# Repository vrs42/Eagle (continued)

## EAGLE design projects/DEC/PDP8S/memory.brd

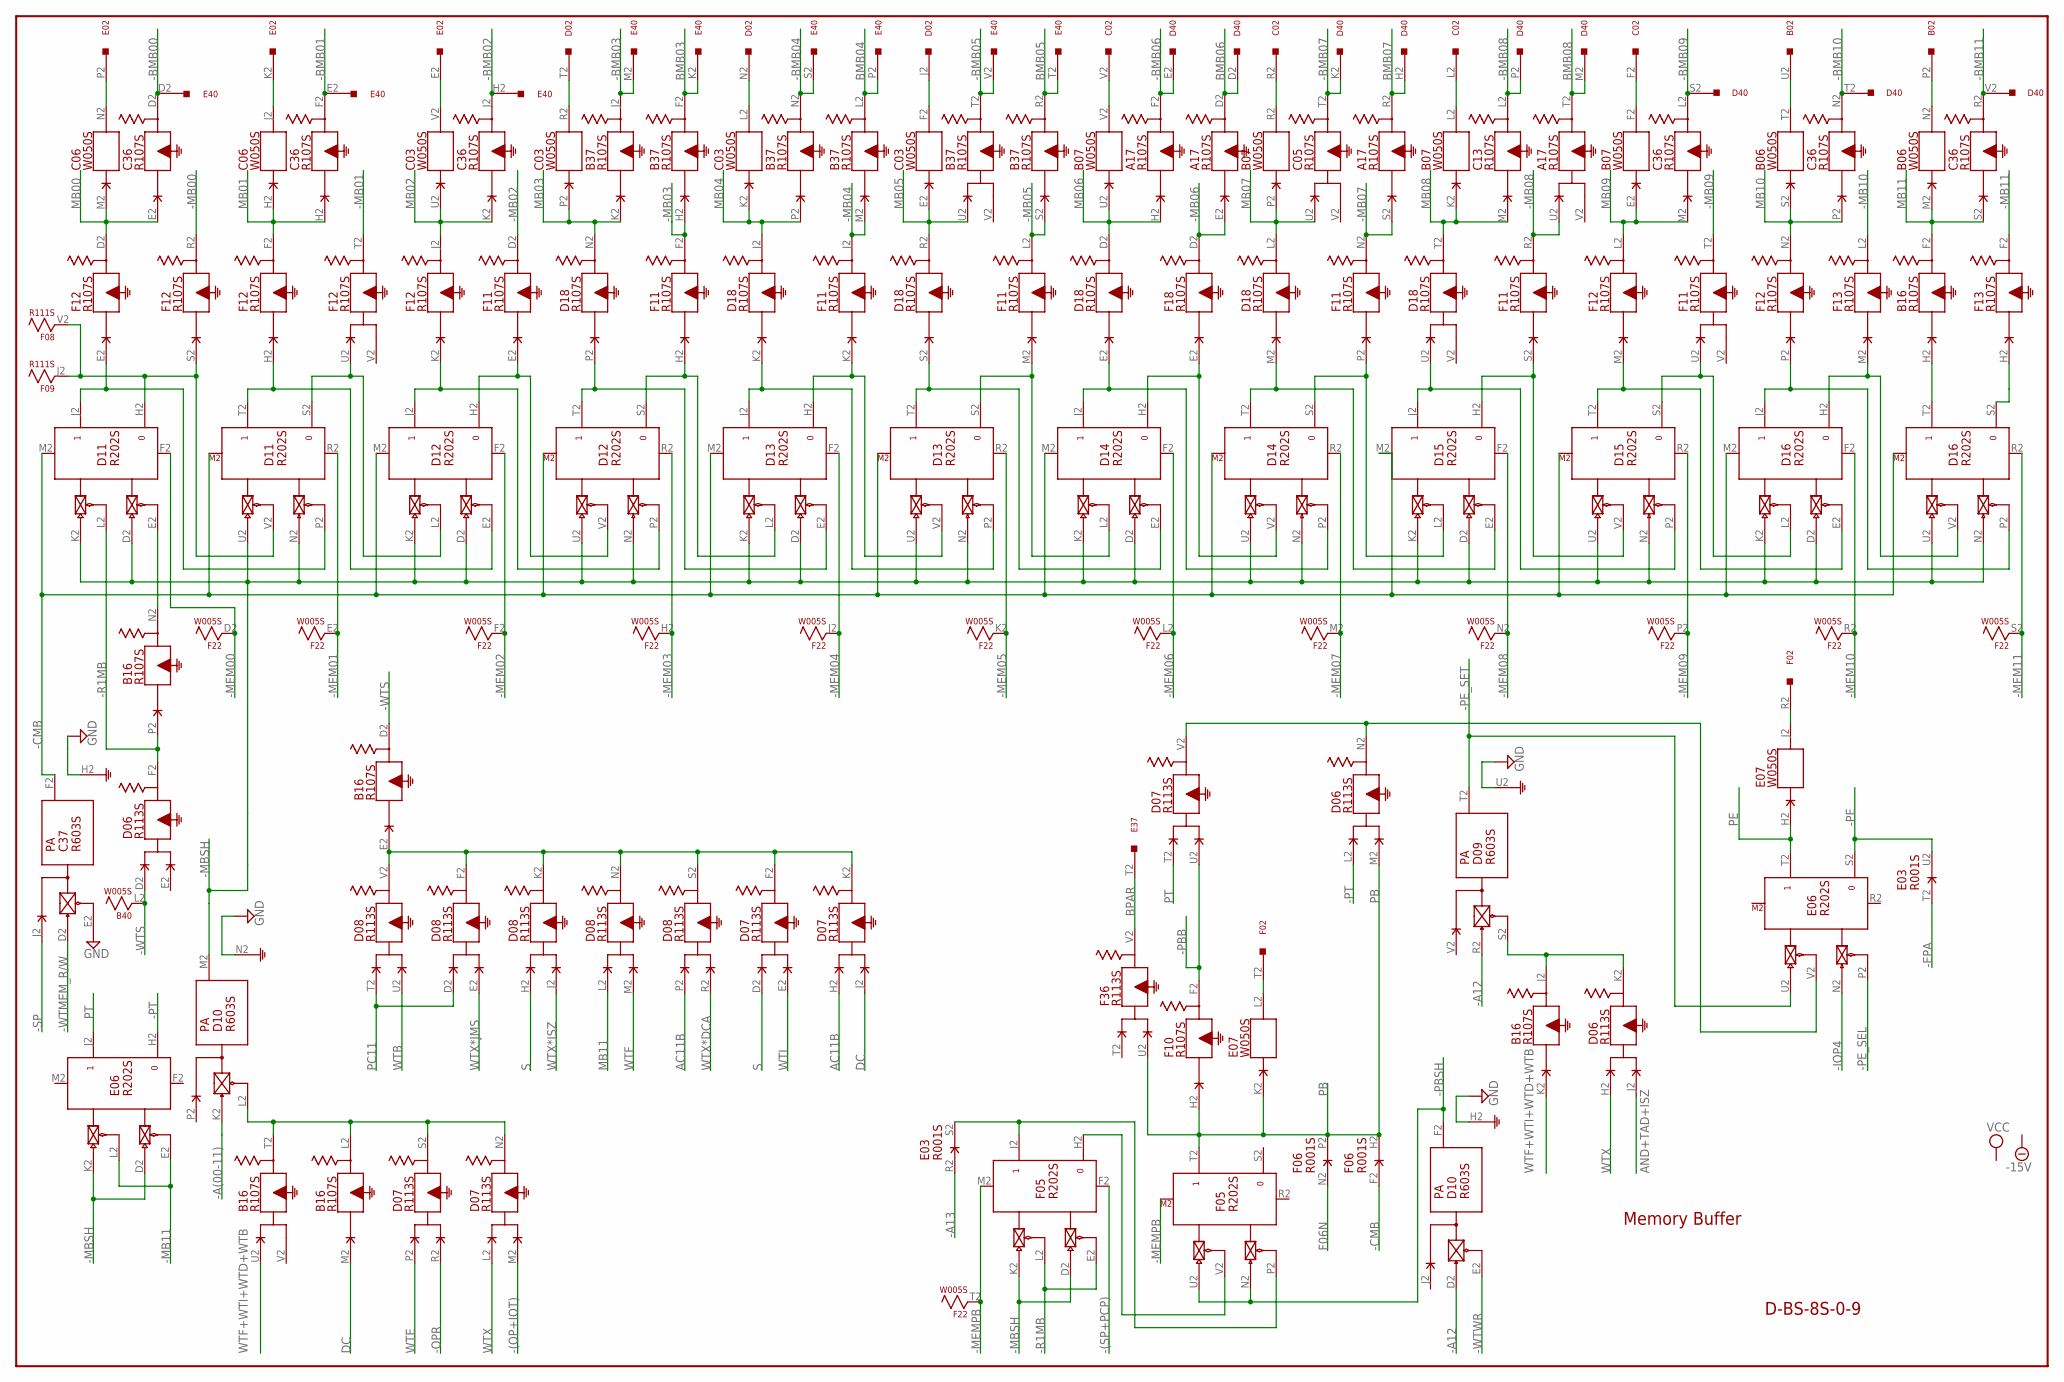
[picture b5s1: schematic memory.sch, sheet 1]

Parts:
A17: R107S; H807S
B02: W023S; H807S
B06, B07: W050S; H807S
B16, B37: R107S; H807S
B40: W005S; H807S
C02: W023S; H807S
C03, C06: W050S; H807S
C05, C13, C36: R107S; H807S
C37: R603S; H807S
D02: W023S; H807S
D06, D07, D08: R113S; H807S
D09, D10: R603S; H807S
D11, D12, D13, D14, D15, D16: R202S; H807S
D18: R107S; H807S
D40: W028S; H807S
E02: W023S; H807S
E03: R001S; H807S
E06: R202S; H807S
E07: W050S; H807S
E37, E40: W028S; H807S
F02: W023S; H807S
F05: R202S; H807S
F06: R001S; H807S
F08, F09: R111S; H807S
F10, F11, F12, F13, F18: R107S; H807S
F22: W005S; H807S
F36: R113S; H807S

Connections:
-15V: A17.B2 (-15V), B06.B2 (-15V), B07.B2 (-15V), B16.B2 (-15V), B37.B2 (-15V), B40.B2 (-15V), C03.B2 (-15V), C05.B2 (-15V), C06.B2 (-15V), C13.B2 (-15V), C36.B2 (-15V), C37.B2 (-15V), D06.B2 (-15V), D07.B2 (-15V), D08.B2 (-15V), D09.B2 (-15V), D10.B2 (-15V), D11.B2 (-15V), D12.B2 (-15V), D13.B2 (-15V), D14.B2 (-15V), D15.B2 (-15V), D16.B2 (-15V), D18.B2 (-15V), E03.B2 (-15V), E06.B2 (-15V), E07.B2 (-15V), F05.B2 (-15V), F06.B2 (-15V), F08.B2 (-15V), F09.B2 (-15V), F10.B2 (-15V), F11.B2 (-15V), F12.B2 (-15V), F13.B2 (-15V), F18.B2 (-15V), F22.B2 (-15V), F36.B2 (-15V); also elsewhere on the board
-(OP+IOT): D07.M2; also elsewhere on the board
-(SP+PCP): F05.F2 (RESET); also elsewhere on the board
-A12: D09.R2 (PU0), D10.D2 (PU0); also elsewhere on the board
-A13: E03.R2 (D); also elsewhere on the board
-A(00-11): D10.K2 (PU0); also elsewhere on the board
-BMB00: C36.D2, E40.D2
-BMB01: C36.F2, E40.E2
-BMB02: C36.J2, E40.H2
-BMB03: B37.J2, E40.M2
-BMB04: B37.N2, E40.S2
-BMB05: B37.T2, E40.V2
-BMB06: A17.F2, D40.E2
-BMB07: C05.T2, D40.K2
-BMB08: C13.L2, D40.P2
-BMB09: C36.L2, D40.S2
-BMB10: C36.N2, D40.T2
-BMB11: C36.R2, D40.V2
-CMB: C37.F2 (O), D11.M2 (SET), D12.M2 (SET), D13.M2 (SET), D14.M2 (SET), D15.M2 (SET), D16.M2 (SET), F06.F2 (D)
-EPA: E03.T2 (D); also elsewhere on the board
-IOP4: E06.N2 (PU0); also elsewhere on the board
-MB00: F12.R2; also elsewhere on the board
-MB01: F12.T2; also elsewhere on the board
-MB02: F11.D2; also elsewhere on the board
-MB03: B37.H2, F11.F2; also elsewhere on the board
-MB04: B37.M2, F11.J2; also elsewhere on the board
-MB05: B37.S2, F11.L2; also elsewhere on the board
-MB06: A17.E2, F18.D2; also elsewhere on the board
-MB07: A17.S2, F11.N2; also elsewhere on the board
-MB08: A17.U2, F11.R2; also elsewhere on the board
-MB09: F11.T2; also elsewhere on the board
-MB10: F13.L2; also elsewhere on the board
-MB11: E06.E2 (EN0), E06.L2 (EN1), F13.F2; also elsewhere on the board
-MBSH: D10.M2 (O), D11.D2 (PU0), D11.K2 (PU1), D11.N2 (PU0), D11.U2 (PU1), D12.D2 (PU0), D12.K2 (PU1), D12.N2 (PU0), D12.U2 (PU1), D13.D2 (PU0), D13.K2 (PU1), D13.N2 (PU0), D13.U2 (PU1), D14.D2 (PU0), D14.K2 (PU1), D14.N2 (PU0), D14.U2 (PU1), D15.D2 (PU0), D15.K2 (PU1), D15.N2 (PU0), D15.U2 (PU1), D16.D2 (PU0), D16.K2 (PU1), D16.N2 (PU0), D16.U2 (PU1), E06.D2 (PU0), E06.K2 (PU1), F05.D2 (PU0), F05.K2 (PU1)
-MEM00: D11.F2 (RESET), F22.D2; also elsewhere on the board
-MEM01: D11.R2 (RESET), F22.E2; also elsewhere on the board
-MEM02: D12.F2 (RESET), F22.F2; also elsewhere on the board
-MEM03: D12.R2 (RESET), F22.H2; also elsewhere on the board
-MEM04: D13.F2 (RESET), F22.J2; also elsewhere on the board
-MEM05: D13.R2 (RESET), F22.K2; also elsewhere on the board
-MEM06: D14.F2 (RESET), F22.L2; also elsewhere on the board
-MEM07: D14.R2 (RESET), F22.M2; also elsewhere on the board
-MEM08: D15.F2 (RESET), F22.N2; also elsewhere on the board
-MEM09: D15.R2 (RESET), F22.P2; also elsewhere on the board
-MEM10: D16.F2 (RESET), F22.R2; also elsewhere on the board
-MEM11: D16.R2 (RESET), F22.S2; also elsewhere on the board
-MEMPB: F05.M2 (SET), F22.T2; also elsewhere on the board
-OPR: D07.R2; also elsewhere on the board
-PBB: D07.U2, F10.F2; also elsewhere on the board
-PBSH: D10.F2 (O), F05.N2 (PU0), F05.U2 (PU1)
-PE: E03.U2 (E), E06.S2 (0); also elsewhere on the board
-PE_SEL: E06.P2 (EN0); also elsewhere on the board
-PE_SET: D09.T2 (O), E06.U2 (PU1)
-PT: D06.L2, E06.H2 (0)
-R1MB: B16.P2, D06.F2, D11.L2 (EN1), F05.E2 (EN0), F05.L2 (EN1)
-SP: C37.J2; also elsewhere on the board
-WTMEM_R/W: C37.D2 (PU0); also elsewhere on the board
-WTS: B16.D2, B40.L2, D06.D2; also elsewhere on the board
-WTWR: D10.E2 (EN0); also elsewhere on the board
AC11B: D07.H2, D08.P2; also elsewhere on the board
AND+TAD+ISZ: D06.J2; also elsewhere on the board
BMB03: B37.F2, E40.K2
BMB04: B37.L2, E40.P2
BMB05: B37.R2, E40.T2
BMB06: A17.D2, D40.D2
BMB07: A17.R2, D40.H2
BMB08: A17.T2, D40.M2
BPAR: E37.T2, F36.V2
DC: B16.M2, D07.J2; also elsewhere on the board
F06N: F06.N2 (D)
GND: A17.C2 (GND), B06.C2 (GND), B07.C2 (GND), B16.C2 (GND), B37.C2 (GND), B40.C2 (GND), C03.C2 (GND), C05.C2 (GND), C06.C2 (GND), C13.C2 (GND), C36.C2 (GND), C37.C2 (GND), C37.E2 (EN0), C37.H2 (G), D06.C2 (GND), D07.C2 (GND), D08.C2 (GND), D09.C2 (GND), D09.U2 (G), D10.C2 (GND), D10.H2 (G), D10.N2 (G), D11.C2 (GND), D12.C2 (GND), D13.C2 (GND), D14.C2 (GND), D15.C2 (GND), D16.C2 (GND), D18.C2 (GND), D40.C2 (GND), D40.F2 (GND), D40.J2 (GND), D40.L2 (GND), D40.N2 (GND), D40.R2 (GND), D40.U2 (GND), E03.C2 (GND), E06.C2 (GND), E07.C2 (GND), E37.C2 (GND), E37.F2 (GND), E37.J2 (GND), E37.L2 (GND), E37.N2 (GND), E37.R2 (GND), E37.U2 (GND), E40.C2 (GND), E40.F2 (GND), E40.J2 (GND), E40.L2 (GND), E40.N2 (GND), E40.R2 (GND), E40.U2 (GND), F05.C2 (GND), F06.C2 (GND), F08.C2 (GND), F09.C2 (GND), F10.C2 (GND), F11.C2 (GND), F12.C2 (GND), F13.C2 (GND), F18.C2 (GND), F22.C2 (GND), F36.C2 (GND); also elsewhere on the board
MB00: C06.M2, C36.E2, F12.D2
MB01: C06.H2, C36.H2, F12.F2
MB02: C03.U2, C36.K2, F12.J2
MB03: B37.K2, C03.P2, D18.N2
MB04: B37.P2, C03.K2, D18.J2; also elsewhere on the board
MB05: B37.U2, C03.E2, D18.R2; also elsewhere on the board
MB06: A17.H2, B07.U2, D18.D2; also elsewhere on the board
MB07: B07.P2, C05.U2, D18.L2; also elsewhere on the board
MB08: B07.K2, C13.M2, D18.T2; also elsewhere on the board
MB09: B07.E2, C36.M2, F12.L2; also elsewhere on the board
MB10: B06.S2, C36.P2, F12.N2; also elsewhere on the board
MB11: B06.M2, B16.F2, C36.S2, D08.L2; also elsewhere on the board
unnamed: D11.J2 (1), D11.P2 (EN0), F12.E2
unnamed: C06.N2, E02.P2
unnamed: D11.H2 (0), D11.V2 (EN1), F08.V2, F09.J2, F12.S2
unnamed: D11.T2 (1), D12.E2 (EN0), F12.H2
unnamed: B16.E2, D07.F2, D07.K2, D08.F2, D08.K2, D08.N2, D08.S2, D08.V2
unnamed: D12.J2 (1), D12.P2 (EN0), F12.K2
unnamed: D12.T2 (1), D13.E2 (EN0), D18.P2
unnamed: D13.J2 (1), D13.P2 (EN0), D18.K2
unnamed: D13.T2 (1), D14.E2 (EN0), D18.S2
unnamed: D14.J2 (1), D14.P2 (EN0), D18.E2
unnamed: D14.T2 (1), D15.E2 (EN0), D18.M2
unnamed: D15.J2 (1), D15.P2 (EN0), D18.U2
unnamed: D15.H2 (0), D15.V2 (EN1), F11.S2
unnamed: D14.S2 (0), D15.L2 (EN1), F11.P2
unnamed: D14.H2 (0), D14.V2 (EN1), F18.E2
unnamed: D13.S2 (0), D14.L2 (EN1), F11.M2
unnamed: D15.T2 (1), D16.E2 (EN0), F12.M2
unnamed: D15.S2 (0), D16.L2 (EN1), F11.U2
unnamed: D16.J2 (1), D16.P2 (EN0), F12.P2
unnamed: D13.H2 (0), D13.V2 (EN1), F11.K2
unnamed: D12.S2 (0), D13.L2 (EN1), F11.H2
unnamed: D12.H2 (0), D12.V2 (EN1), F11.E2
unnamed: D11.S2 (0), D12.L2 (EN1), F12.U2
unnamed: D16.H2 (0), D16.V2 (EN1), F13.M2
unnamed: B16.H2, D16.T2 (1)
unnamed: D16.S2 (0), F13.H2
unnamed: C06.J2, E02.K2
unnamed: C03.V2, E02.E2
unnamed: C03.R2, D02.T2
unnamed: C03.L2, D02.N2
unnamed: C03.F2, D02.J2
unnamed: B07.V2, C02.V2
unnamed: B07.R2, C02.R2
unnamed: B07.L2, C02.L2
unnamed: B07.F2, C02.F2
unnamed: B02.U2, B06.T2
unnamed: B02.P2, B06.N2
unnamed: B16.L2, B16.T2, D07.N2, D07.S2, D10.L2 (EN0)
unnamed: B16.N2, D11.E2 (EN0)
unnamed: B16.J2, D06.K2, D09.S2 (EN0)
unnamed: E07.J2, F02.R2
unnamed: D06.N2, D07.V2, E06.V2 (EN1)
unnamed: E07.L2, F02.T2
unnamed: F05.H2 (0), F05.V2 (EN1)
unnamed: E03.S2 (E), F05.J2 (1), F05.P2 (EN0)
PB: D06.M2, E07.K2, F05.T2 (1), F06.H2 (E), F06.P2 (E), F10.H2, F36.U2
PC11: D08.D2, D08.T2; also elsewhere on the board
PE: E06.T2 (1), E07.H2; also elsewhere on the board
PT: D07.T2, E06.J2 (1)
S: D07.D2, D08.H2; also elsewhere on the board
VCC: A17.A2 (VCC), B06.A2 (VCC), B07.A2 (VCC), B16.A2 (VCC), B37.A2 (VCC), B40.A2 (VCC), C03.A2 (VCC), C05.A2 (VCC), C06.A2 (VCC), C13.A2 (VCC), C36.A2 (VCC), C37.A2 (VCC), D06.A2 (VCC), D07.A2 (VCC), D08.A2 (VCC), D09.A2 (VCC), D10.A2 (VCC), D11.A2 (VCC), D12.A2 (VCC), D13.A2 (VCC), D14.A2 (VCC), D15.A2 (VCC), D16.A2 (VCC), D18.A2 (VCC), E03.A2 (VCC), E06.A2 (VCC), E07.A2 (VCC), F05.A2 (VCC), F06.A2 (VCC), F08.A2 (VCC), F09.A2 (VCC), F10.A2 (VCC), F11.A2 (VCC), F12.A2 (VCC), F13.A2 (VCC), F18.A2 (VCC), F22.A2 (VCC), F36.A2 (VCC); also elsewhere on the board
WTB: D08.U2; also elsewhere on the board
WTE: D07.P2; also elsewhere on the board
WTF: D08.M2; also elsewhere on the board
WTF+WTI+WTD+WTB: B16.K2, B16.U2; also elsewhere on the board
WTI: D07.E2; also elsewhere on the board
WTX: D06.H2, D07.L2; also elsewhere on the board
WTX*DCA: D08.R2; also elsewhere on the board
WTX*ISZ: D08.J2; also elsewhere on the board
WTX*JMS: D08.E2; also elsewhere on the board

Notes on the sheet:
D-BS-8S-0-9
Memory Buffer

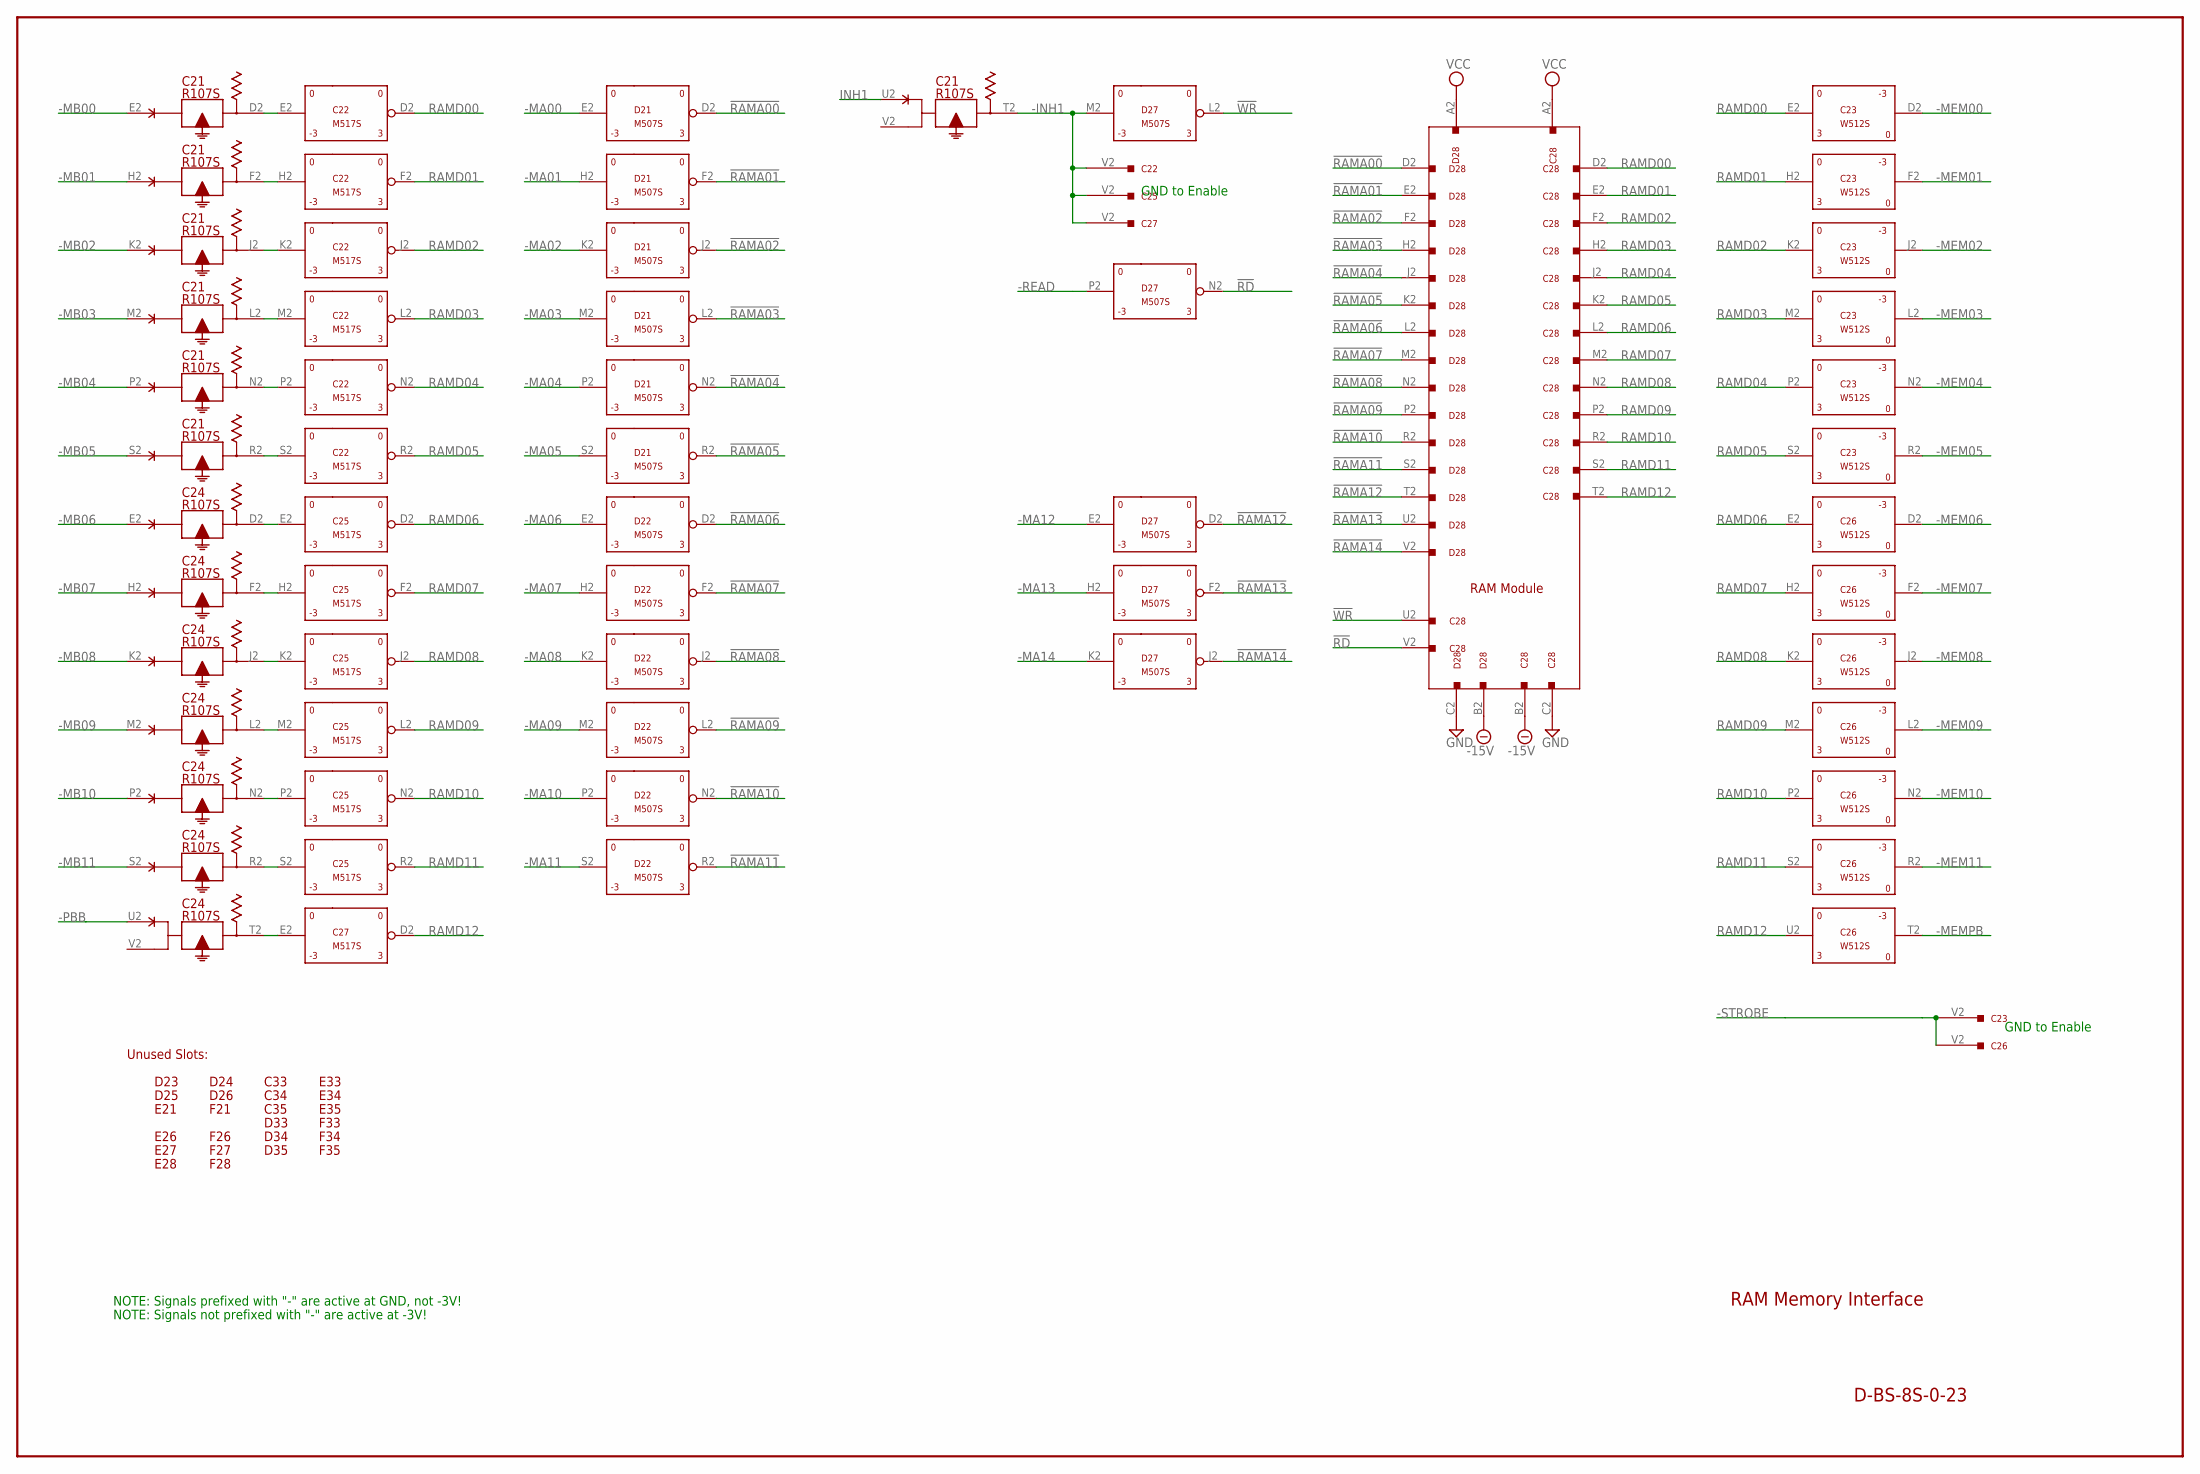
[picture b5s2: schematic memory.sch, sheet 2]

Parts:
C21, C24: R107S; H807S
C22, C25, C27: M517S; H807S
C23, C26: W512S; H807S
C28: W023S; H807S
C33, C34, C35: EMPTYS; H807S
D21, D22, D27: M507S; H807S
D23, D24, D25, D26, D33, D34, D35: EMPTYS; H807S
D28: W023S; H807S
E21, E26, E27, E28, E33, E34, E35: EMPTYS; H807S
F21, F26, F27, F28, F33, F34, F35: EMPTYS; H807S

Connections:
!RAMA00: D21.D2 (OUT), D28.D2
!RAMA01: D21.F2 (OUT), D28.E2
!RAMA02: D21.J2 (OUT), D28.F2
!RAMA03: D21.L2 (OUT), D28.H2
!RAMA04: D21.N2 (OUT), D28.J2
!RAMA05: D21.R2 (OUT), D28.K2
!RAMA06: D22.D2 (OUT), D28.L2
!RAMA07: D22.F2 (OUT), D28.M2
!RAMA08: D22.J2 (OUT), D28.N2
!RAMA09: D22.L2 (OUT), D28.P2
!RAMA10: D22.N2 (OUT), D28.R2
!RAMA11: D22.R2 (OUT), D28.S2
!RAMA12: D27.D2 (OUT), D28.T2
!RAMA13: D27.F2 (OUT), D28.U2
!RAMA14: D27.J2 (OUT), D28.V2
!RD: C28.V2, D27.N2 (OUT)
!WR: C28.U2, D27.L2 (OUT)
-15V: C21.B2 (-15V), C22.B2 (-15V), C23.B2 (-15V), C24.B2 (-15V), C25.B2 (-15V), C26.B2 (-15V), C27.B2 (-15V), C28.B2, C33.B2 (-15V), C34.B2 (-15V), C35.B2 (-15V), D21.B2 (-15V), D22.B2 (-15V), D23.B2 (-15V), D24.B2 (-15V), D25.B2 (-15V), D26.B2 (-15V), D27.B2 (-15V), D28.B2, D33.B2 (-15V), D34.B2 (-15V), D35.B2 (-15V), E21.B2 (-15V), E26.B2 (-15V), E27.B2 (-15V), E28.B2 (-15V), E33.B2 (-15V), E34.B2 (-15V), E35.B2 (-15V), F21.B2 (-15V), F26.B2 (-15V), F27.B2 (-15V), F28.B2 (-15V), F33.B2 (-15V), F34.B2 (-15V), F35.B2 (-15V); also elsewhere on the board
-INH1: C21.T2, C22.V2, C25.V2, C27.V2, D27.M2 (IN)
-MA00: D21.E2 (IN); also elsewhere on the board
-MA01: D21.H2 (IN); also elsewhere on the board
-MA02: D21.K2 (IN); also elsewhere on the board
-MA03: D21.M2 (IN); also elsewhere on the board
-MA04: D21.P2 (IN); also elsewhere on the board
-MA05: D21.S2 (IN); also elsewhere on the board
-MA06: D22.E2 (IN); also elsewhere on the board
-MA07: D22.H2 (IN); also elsewhere on the board
-MA08: D22.K2 (IN); also elsewhere on the board
-MA09: D22.M2 (IN); also elsewhere on the board
-MA10: D22.P2 (IN); also elsewhere on the board
-MA11: D22.S2 (IN); also elsewhere on the board
-MA12: D27.E2 (IN)
-MA13: D27.H2 (IN)
-MA14: D27.K2 (IN)
-MB00: C21.E2; also elsewhere on the board
-MB01: C21.H2; also elsewhere on the board
-MB02: C21.K2; also elsewhere on the board
-MB03: C21.M2; also elsewhere on the board
-MB04: C21.P2; also elsewhere on the board
-MB05: C21.S2; also elsewhere on the board
-MB06: C24.E2; also elsewhere on the board
-MB07: C24.H2; also elsewhere on the board
-MB08: C24.K2; also elsewhere on the board
-MB09: C24.M2; also elsewhere on the board
-MB10: C24.P2; also elsewhere on the board
-MB11: C24.S2; also elsewhere on the board
-MEM00: C23.D2 (OUT); also elsewhere on the board
-MEM01: C23.F2 (OUT); also elsewhere on the board
-MEM02: C23.J2 (OUT); also elsewhere on the board
-MEM03: C23.L2 (OUT); also elsewhere on the board
-MEM04: C23.N2 (OUT); also elsewhere on the board
-MEM05: C23.R2 (OUT); also elsewhere on the board
-MEM06: C26.D2 (OUT); also elsewhere on the board
-MEM07: C26.F2 (OUT); also elsewhere on the board
-MEM08: C26.J2 (OUT); also elsewhere on the board
-MEM09: C26.L2 (OUT); also elsewhere on the board
-MEM10: C26.N2 (OUT); also elsewhere on the board
-MEM11: C26.R2 (OUT); also elsewhere on the board
-MEMPB: C26.T2 (OUT); also elsewhere on the board
-PBB: C24.U2; also elsewhere on the board
-READ: D27.P2 (IN); also elsewhere on the board
-STROBE: C23.V2, C26.V2; also elsewhere on the board
GND: C21.C2 (GND), C22.C2 (GND), C22.T2 (GND), C22.U2 (GND), C23.C2 (GND), C24.C2 (GND), C25.C2 (GND), C25.T2 (GND), C25.U2 (GND), C26.C2 (GND), C27.C2 (GND), C27.T2 (GND), C27.U2 (GND), C28.C2, C33.C2 (GND), C34.C2 (GND), C35.C2 (GND), D21.C2 (GND), D22.C2 (GND), D23.C2 (GND), D24.C2 (GND), D25.C2 (GND), D26.C2 (GND), D27.C2 (GND), D28.C2, D33.C2 (GND), D34.C2 (GND), D35.C2 (GND), E21.C2 (GND), E26.C2 (GND), E27.C2 (GND), E28.C2 (GND), E33.C2 (GND), E34.C2 (GND), E35.C2 (GND), F21.C2 (GND), F26.C2 (GND), F27.C2 (GND), F28.C2 (GND), F33.C2 (GND), F34.C2 (GND), F35.C2 (GND); also elsewhere on the board
INH1: C21.U2; also elsewhere on the board
unnamed: C24.D2, C25.E2 (IN)
unnamed: C21.R2, C22.S2 (IN)
unnamed: C21.N2, C22.P2 (IN)
unnamed: C21.L2, C22.M2 (IN)
unnamed: C21.J2, C22.K2 (IN)
unnamed: C21.F2, C22.H2 (IN)
unnamed: C21.D2, C22.E2 (IN)
unnamed: C24.F2, C25.H2 (IN)
unnamed: C24.J2, C25.K2 (IN)
unnamed: C24.L2, C25.M2 (IN)
unnamed: C24.N2, C25.P2 (IN)
unnamed: C24.R2, C25.S2 (IN)
unnamed: C24.T2, C27.E2 (IN)
RAMD00: C22.D2 (OUT), C23.E2 (IN), C28.D2
RAMD01: C22.F2 (OUT), C23.H2 (IN), C28.E2
RAMD02: C22.J2 (OUT), C23.K2 (IN), C28.F2
RAMD03: C22.L2 (OUT), C23.M2 (IN), C28.H2
RAMD04: C22.N2 (OUT), C23.P2 (IN), C28.J2
RAMD05: C22.R2 (OUT), C23.S2 (IN), C28.K2
RAMD06: C25.D2 (OUT), C26.E2 (IN), C28.L2
RAMD07: C25.F2 (OUT), C26.H2 (IN), C28.M2
RAMD08: C25.J2 (OUT), C26.K2 (IN), C28.N2
RAMD09: C25.L2 (OUT), C26.M2 (IN), C28.P2
RAMD10: C25.N2 (OUT), C26.P2 (IN), C28.R2
RAMD11: C25.R2 (OUT), C26.S2 (IN), C28.S2
RAMD12: C26.U2 (IN), C27.D2 (OUT), C28.T2
VCC: C21.A2 (VCC), C22.A2 (VCC), C23.A2 (VCC), C24.A2 (VCC), C25.A2 (VCC), C26.A2 (VCC), C27.A2 (VCC), C28.A2, C33.A2 (VCC), C34.A2 (VCC), C35.A2 (VCC), D21.A2 (VCC), D22.A2 (VCC), D23.A2 (VCC), D24.A2 (VCC), D25.A2 (VCC), D26.A2 (VCC), D27.A2 (VCC), D28.A2, D33.A2 (VCC), D34.A2 (VCC), D35.A2 (VCC), E21.A2 (VCC), E26.A2 (VCC), E27.A2 (VCC), E28.A2 (VCC), E33.A2 (VCC), E34.A2 (VCC), E35.A2 (VCC), F21.A2 (VCC), F26.A2 (VCC), F27.A2 (VCC), F28.A2 (VCC), F33.A2 (VCC), F34.A2 (VCC), F35.A2 (VCC); also elsewhere on the board

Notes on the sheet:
RAM Module
Unused Slots:
GND to Enable
NOTE: Signals prefixed with "-" are active at GND, not -3V!
NOTE: Signals not prefixed with "-" are active at -3V!
D-BS-8S-0-23
RAM Memory Interface

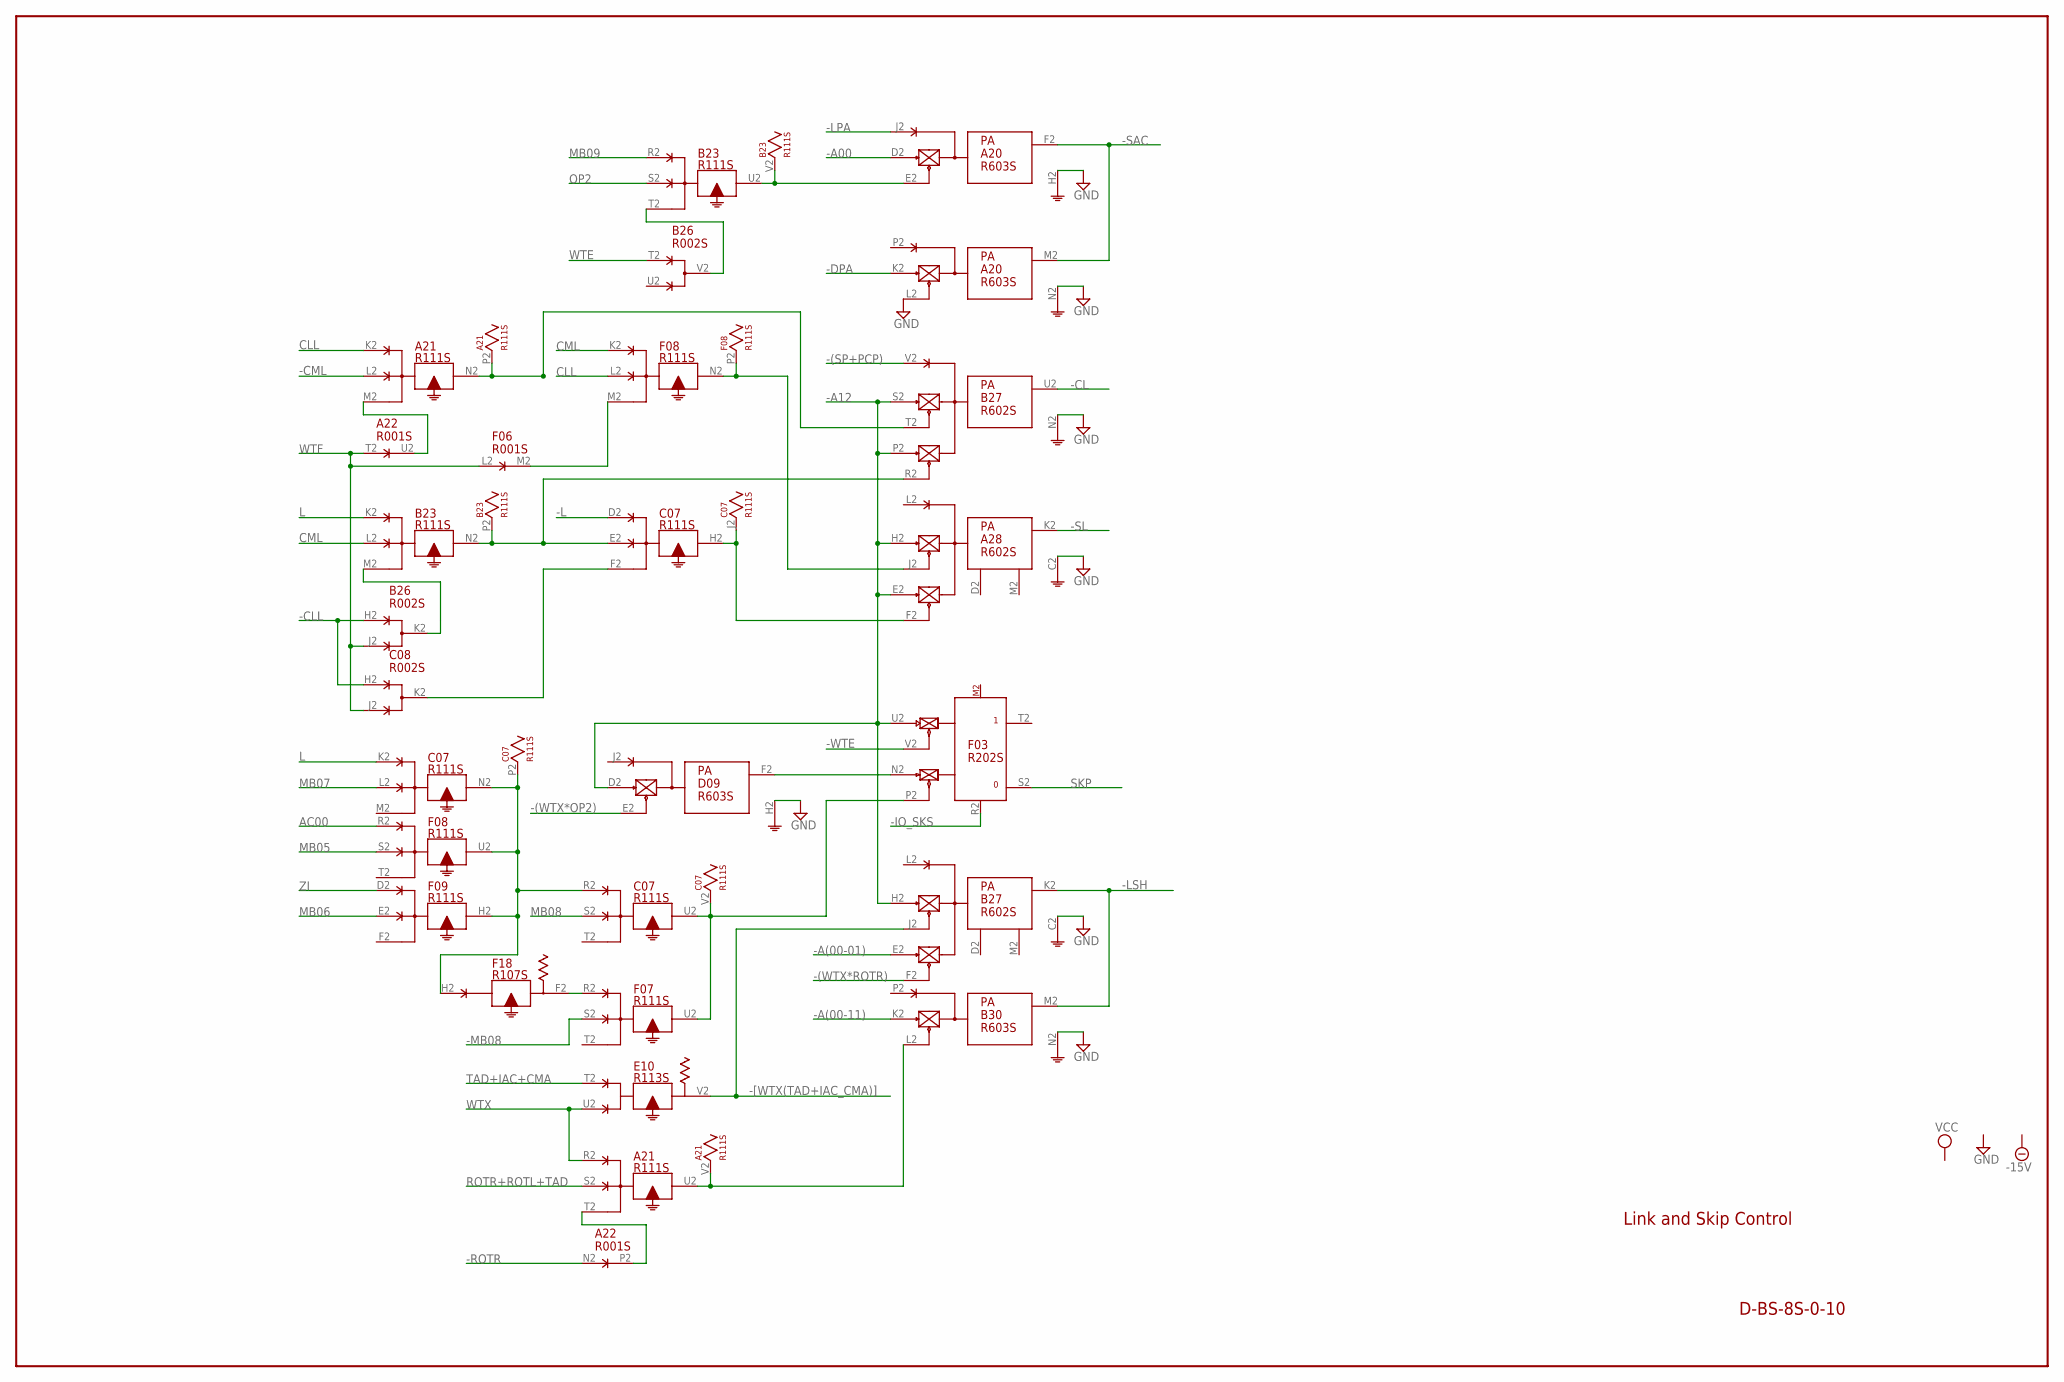
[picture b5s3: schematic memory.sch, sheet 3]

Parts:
A20: R603S; H807S
A21: R111S; H807S
A22: R001S; H807S
A28: R602S; H807S
B23: R111S; H807S
B26: R002S; H807S
B27: R602S; H807S
B30: R603S; H807S
C07: R111S; H807S
C08: R002S; H807S
D09: R603S; H807S
E10: R113S; H807S
F03: R202S; H807S
F06: R001S; H807S
F07, F08, F09: R111S; H807S
F18: R107S; H807S

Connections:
-15V: A20.B2 (-15V), A21.B2 (-15V), A22.B2 (-15V), A28.B2 (-15V), B23.B2 (-15V), B26.B2 (-15V), B27.B2 (-15V), B30.B2 (-15V), C07.B2 (-15V), C08.B2 (-15V), D09.B2 (-15V), E10.B2 (-15V), F03.B2 (-15V), F06.B2 (-15V), F07.B2 (-15V), F08.B2 (-15V), F09.B2 (-15V), F18.B2 (-15V); also elsewhere on the board
-(SP+PCP): B27.V2 (L); also elsewhere on the board
-(WTX*OP2): D09.E2 (EN0); also elsewhere on the board
-(WTX*ROTR): B27.F2 (F); also elsewhere on the board
-A00: A20.D2 (PU0); also elsewhere on the board
-A12: A28.E2 (E), A28.H2 (H), B27.H2 (H), B27.P2 (E), B27.S2 (H), D09.D2 (PU0), F03.U2 (PU1); also elsewhere on the board
-A(00-01): B27.E2 (E); also elsewhere on the board
-A(00-11): B30.K2 (PU0); also elsewhere on the board
-CL: B27.U2 (K); also elsewhere on the board
-CLL: B26.H2 (D), C08.H2 (D); also elsewhere on the board
-CML: A21.L2; also elsewhere on the board
-DPA: A20.K2 (PU0); also elsewhere on the board
-IO_SKS: F03.R2 (RESET); also elsewhere on the board
-L: C07.D2; also elsewhere on the board
-LPA: A20.J2; also elsewhere on the board
-LSH: B27.K2 (K), B30.M2 (O); also elsewhere on the board
-MB08: F07.S2; also elsewhere on the board
-ROTR: A22.N2 (D); also elsewhere on the board
-SAC: A20.F2 (O), A20.M2 (O); also elsewhere on the board
-SL: A28.K2 (K); also elsewhere on the board
-WTE: F03.V2 (EN1); also elsewhere on the board
-[WTX(TAD+IAC_CMA)]: B27.J2 (J), E10.V2
AC00: F08.R2; also elsewhere on the board
CLL: A21.K2, F08.L2; also elsewhere on the board
CML: B23.L2, F08.K2; also elsewhere on the board
GND: A20.C2 (GND), A20.H2 (G), A20.L2 (EN0), A20.N2 (G), A21.C2 (GND), A22.C2 (GND), A28.C2 (GND), B23.C2 (GND), B26.C2 (GND), B27.C2 (GND), B27.N2 (C), B30.C2 (GND), B30.N2 (G), C07.C2 (GND), C08.C2 (GND), D09.C2 (GND), D09.H2 (G), E10.C2 (GND), F03.C2 (GND), F06.C2 (GND), F07.C2 (GND), F08.C2 (GND), F09.C2 (GND), F18.C2 (GND); also elsewhere on the board
L: B23.K2, C07.K2; also elsewhere on the board
MB05: F08.S2; also elsewhere on the board
MB06: F09.E2; also elsewhere on the board
MB07: C07.L2; also elsewhere on the board
MB08: C07.S2; also elsewhere on the board
MB09: B23.R2; also elsewhere on the board
unnamed: A20.E2 (EN0), B23.U2, B23.V2
unnamed: B23.T2, B26.V2 (F)
unnamed: A28.J2 (J), F08.N2, F08.P2
unnamed: A21.N2, A21.P2, B27.T2 (J)
unnamed: B23.N2, B23.P2, B27.R2 (F), C07.E2
unnamed: A28.F2 (F), C07.H2, C07.J2
unnamed: B23.M2, B26.K2 (F)
unnamed: F06.M2 (E), F08.M2
unnamed: C07.F2, C08.K2 (F)
unnamed: D09.F2 (O), F03.N2 (PU0)
unnamed: C07.U2, C07.V2, F03.P2 (EN0), F07.U2
unnamed: F07.R2, F18.F2
unnamed: C07.N2, C07.P2, C07.R2, F08.U2, F09.H2, F18.H2
unnamed: A21.U2, A21.V2, B30.L2 (EN0)
unnamed: A21.T2, A22.P2 (E)
unnamed: A21.M2, A22.U2 (E)
OP2: B23.S2; also elsewhere on the board
ROTR+ROTL+TAD: A21.S2; also elsewhere on the board
SKP: F03.S2 (0); also elsewhere on the board
TAD+IAC+CMA: E10.T2; also elsewhere on the board
VCC: A20.A2 (VCC), A21.A2 (VCC), A22.A2 (VCC), A28.A2 (VCC), B23.A2 (VCC), B26.A2 (VCC), B27.A2 (VCC), B30.A2 (VCC), C07.A2 (VCC), C08.A2 (VCC), D09.A2 (VCC), E10.A2 (VCC), F03.A2 (VCC), F06.A2 (VCC), F07.A2 (VCC), F08.A2 (VCC), F09.A2 (VCC), F18.A2 (VCC); also elsewhere on the board
WTE: B26.T2 (D); also elsewhere on the board
WTF: A22.T2 (D), B26.J2 (E), C08.J2 (E), F06.L2 (D); also elsewhere on the board
WTX: A21.R2, E10.U2; also elsewhere on the board
ZI: F09.D2; also elsewhere on the board

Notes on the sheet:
Link and Skip Control
D-BS-8S-0-10
